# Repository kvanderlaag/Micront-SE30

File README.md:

# Micron't SE30 Beigescale Adapter
 
Micron XCEED CRT yoke board for internal greyscale on the Macintosh SE/30

If you've miraculously stumbled across one (or two) of the assorted Micron SE/30 PDS video cards which have the connector for internal greyscale output, the piece you may be missing is the board which slaps onto the back of the CRT to let it run greyscale rather than black and white. (Also the associated adapter harness.)
 
As far as I know, these have been cloned many times, and sold by various parties. All of these clones are largely derived from [Gamba's original work to this end](http://web.archive.org/web/20010626004329/http://www.accesscom.com/~gamba/microngray.html), which is no longer actively available, but by the mercy of the [internet gods](https://www.archive.org) still archived. This board doesn't provide anything that the others don't -- it's also just a straight clone, though the routing and component placement is a little more closely derived from [D.S. Larsen's photos of the original Micron board.](http://web.archive.org/web/20010626004329/http://www.eskimo.com/~dslarsen/micron/)
 
The two important things about this design are:
1. That it was created on 14-10-2022, using footprints for parts that are actively available at this time, and
2. _That it actually fuckin' exists on GitHub, with an open license._ 
 
Take it, build it, fix it, improve it, use it to make a death ray; I don't care, just _actually do something with it_, because finding someone who will actually sell you one of these today is _annoyingly difficult_.
 
## Known Issues

There is currently one _massive_ caveat: I haven't actually built one of these yet. Everything appears to be lined up to the original board fairly accurately, and I'm confident in the routing relative to the original board and the schematic, but the one thing that concerns me is the footprint for the tube socket. The footprint was created with [this 7-pin miniature (B7G) tube socket, P/N B7G-PCB](http://www.pacifictv.ca/socket.htm) in mind, since the dimensions are provided, but I've also ordered a couple of tube sockets from Aliexpress; if those don't quite fit, I'll create a second version of the board with an updated footprint, just so that there's options for tube socket sourcing, since that seems like it could be a pain in the ass.

Also, obviously, since I haven't built it yet, there's no guarantee it won't blow up your SE/30, or your video card. Since both of these are quite expensive, maybe double check it against Gamba's (known-working) source material before you go build it. I'm not infallible -- in fact, I'm not even that smart -- but I'm also not your dad, so do what you want.

I still need to create a KiCAD schematic of the adapter harness, too.

## Bill of Materials

If you want to actually build this, you probably need some parts to do so. These are the parts the board was designed for; other parts with similar size, lead spacing, and characteristics will probably work fine.

| Quantity | Reference | Part Number             | Description                                      | Link                                                       | Alternate                                       |
| -------- | --------- | -------------           | -------------------------------------------      | ---------------------------------------------------------- | ----------------------------------------------- |
| 3        | C1,2,3    | CK45-E3AD103ZYVNA       | Capacitor, ceramic disc, 0.01uF 1KVDC            | https://www.mouser.ca/ProductDetail/810-CK45-E3AD103ZYVN   |                                                 |
| 1        | C4        | ESS106M050AE2AA         | Capacitor, electrolytic, 10uF, 50VDC, 105°C      | https://www.mouser.ca/ProductDetail/80-ESS106M050AE2AA     |                                                 |
| 1        | C5        | UVZ1A470MDD             | Capacitor, electrolytic, 47uF, 10VDC, 105°C      | https://www.mouser.ca/ProductDetail/647-UVZ1A470MDD        |                                                 |
| 1        | C6        | R82EC3100DQ70J          | Capacitor, film, 0.1uF, 100VDC                   | https://www.mouser.ca/ProductDetail/80-R82EC3100DQ70J      |                                                 |
| 1        | C7        | K104Z15Y5VE5TL2         | Capacitor, multi-layered ceramic, 0.1uF, 25VDC   | https://www.mouser.ca/ProductDetail/594-K104Z15Y5VE5TL2    |                                                 |
| 1        | C8        | UVZ1C101MDD             | Capacitor, electrolytic, 100uF, 16VDC, 105°C     | https://www.mouser.ca/ProductDetail/647-UVZ1C101MDD        |                                                 |
| 1        | C9        | UPW1J101MPD6            | Capacitor, electrolytic, 100uF, 63VDC, 105°C     | https://www.mouser.ca/ProductDetail/647-UPW1J101MPD6       |                                                 |
| 3        | D1,2,3    | 1N914BTR                | Diode, 1N914A                                    | https://www.mouser.ca/ProductDetail/512-1N914BTR           |                                                 |
| 1        | J1        | 39-29-1088              | Connector, 8 pin, right-angle; Molex 5569 series | https://www.mouser.ca/ProductDetail/538-39-29-1088         |                                                 |
| 2        | L1,2      | 78F270J-RC              | Inductor, 27 uH 5%                               | https://www.mouser.ca/ProductDetail/542-78F270-RC          |                                                 |
| 2        | Q1,2      | 2N5550TFR               | Transistor, NPN                                  | https://www.mouser.ca/ProductDetail/512-2N5550TFR          |                                                 |
| 1        | Q3        | PN2222ABU               | Transistor, NPN                                  | https://www.mouser.ca/ProductDetail/512-PN2222ABU          |                                                 |
| 2        | R1,2      | CFR200JT-73-1K          | Resistor, 1.0K ohms,   2W   5%                   | https://www.mouser.ca/ProductDetail/YAGEO/CFR200JT-73-1K   |                                                 |
| 1        | R3        | CFR-25JB-52-75R         | Resistor,   75 ohms, 1/4W   5%                   | https://www.mouser.ca/ProductDetail/YAGEO/CFR-25JB-52-75R  |                                                 |
| 1        | R4        | CFR-25JR-52-300R        | Resistor,  300 ohms, 1/4W   5%                   | https://www.mouser.ca/ProductDetail/YAGEO/CFR-25JR-52-300R |                                                 |
| 1        | R5        | CFR-25JT-52-56R         | Resistor,   56 ohms, 1/4W   5%                   | https://www.mouser.ca/ProductDetail/YAGEO/CFR-25JT-52-56R  |                                                 |
| 1        | R6        | CFR-25JT-52-200R        | Resistor,  200 ohms, 1/4W   5%                   | https://www.mouser.ca/ProductDetail/YAGEO/CFR-25JT-52-200R |                                                 |
| 1        | R7        | CFR-25JT-52-12K         | Resistor,  12K ohms, 1/4W   5%                   | https://www.mouser.ca/ProductDetail/YAGEO/CFR-25JT-52-12K  |                                                 |
| 1        | R8        | CFR-25JB-52-1K5         | Resistor, 1.5K ohms, 1/4W   5%                   | https://www.mouser.ca/ProductDetail/YAGEO/CFR-25JB-52-1K5  |                                                 |
| 3        | R9,10,11  | CFR50SJT-52-100K        | Resistor, 100K ohms, 1/2W   5%                   | https://www.mouser.ca/ProductDetail/YAGEO/CFR50SJT-52-100K |                                                 |
| 1        | RV1       | PT10LH01-201A2020-S     | Resistor, variable, 200 ohms                     | https://www.mouser.ca/ProductDetail/531-PT10H-200-S        |                                                 |
| 1        | V1        | APCO EIA-1210 / B7G-PCB | Socket, CRT, 7 pin miniature, PC mount           | http://www.pacifictv.ca/socket.htm                         | https://www.aliexpress.com/item/1549957333.html |

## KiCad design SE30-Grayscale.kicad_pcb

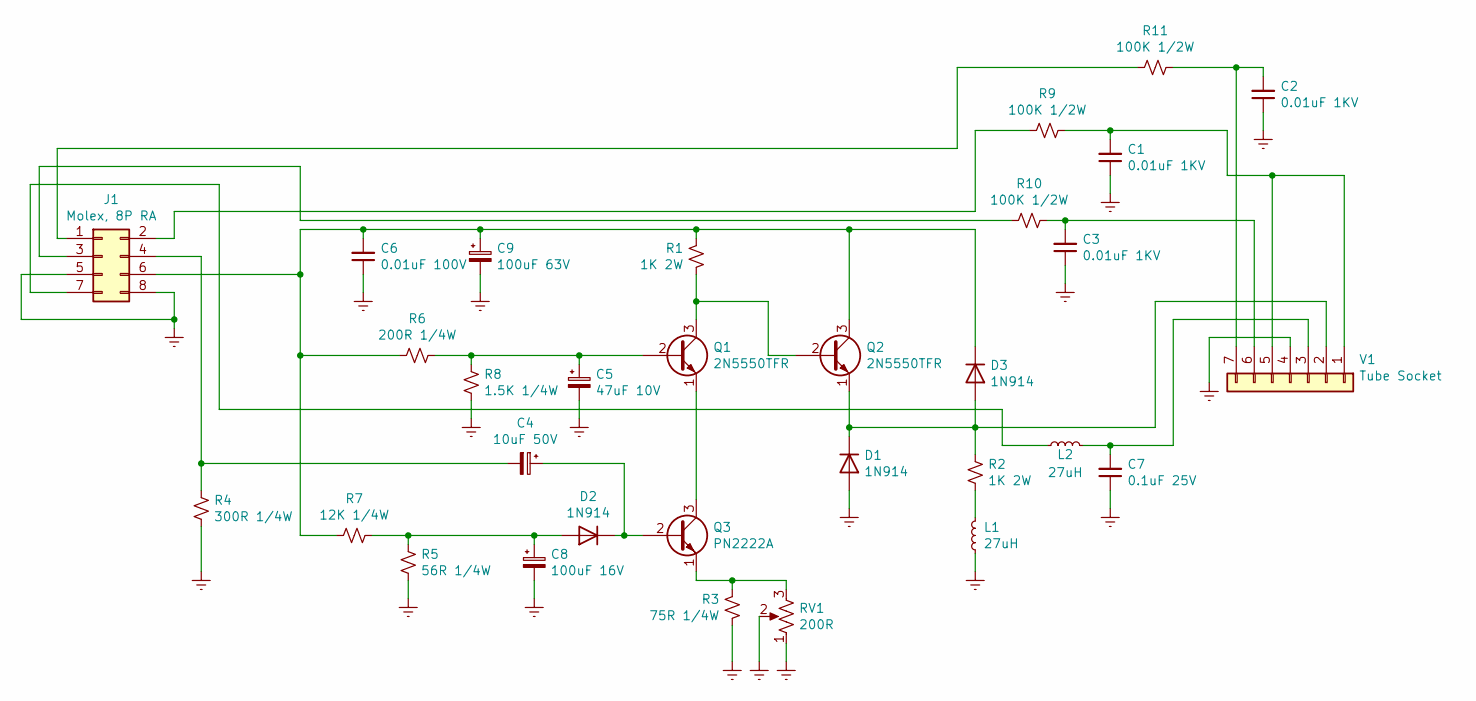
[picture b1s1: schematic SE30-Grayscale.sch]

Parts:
C1, C2, C3: 0.01uF 1KV; C_Disc_D11.0mm_W5.0mm_P7.50mm
C4: 10uF 50V; CP_Radial_D6.3mm_P2.50mm
C5: 47uF 10V; CP_Radial_D5.0mm_P2.00mm
C6: 0.01uF 100V; C_Rect_L7.2mm_W2.5mm_P5.00mm_FKS2_FKP2_MKS2_MKP2
C7: 0.1uF 25V; C_Rect_L4.6mm_W2.0mm_P2.50mm_MKS02_FKP02
C8: 100uF 16V; CP_Radial_D5.0mm_P2.00mm
C9: 100uF 63V; CP_Radial_D8.0mm_P3.50mm
D1, D2, D3: 1N914; D_DO-35_SOD27_P7.62mm_Horizontal
J1: Molex, 8P RA; Molex
L1, L2: 27uH; L_Axial_L7.0mm_D3.3mm_P12.70mm_Horizontal_Fastron_MICC
Q1, Q2: 2N5550TFR; TO-92_Inline_Wide
Q3: PN2222A; TO-92_Inline_Wide
R1, R2: 1K 2W; R_Axial_DIN0617_L17.0mm_D6.0mm_P20.32mm_Horizontal
R3: 75R 1/4W; R_Axial_DIN0207_L6.3mm_D2.5mm_P7.62mm_Horizontal
R4: 300R 1/4W; R_Axial_DIN0207_L6.3mm_D2.5mm_P7.62mm_Horizontal
R5: 56R 1/4W; R_Axial_DIN0207_L6.3mm_D2.5mm_P7.62mm_Horizontal
R6: 200R 1/4W; R_Axial_DIN0207_L6.3mm_D2.5mm_P7.62mm_Horizontal
R7: 12K 1/4W; R_Axial_DIN0207_L6.3mm_D2.5mm_P7.62mm_Horizontal
R8: 1.5K 1/4W; R_Axial_DIN0207_L6.3mm_D2.5mm_P7.62mm_Horizontal
R9, R10, R11: 100K 1/2W; R_Axial_DIN0411_L9.9mm_D3.6mm_P12.70mm_Horizontal
RV1: 200R; Trimmer_Res_Amphenol
V1: Tube Socket; Tube-7pin-Mini

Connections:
Earth: C1.1, C2.1, C3.1, C5.2, C6.1, C7.1, C8.2, C9.2, D1.2 (A), J1.5, J1.8, L1.1, R3.1, R4.1, R5.2, R8.1, RV1.1, RV1.2, V1.4
unnamed: C1.2, R9.1, V1.1, V1.5
unnamed: C2.2, R11.1, V1.7
unnamed: C3.2, R10.1, V1.6
unnamed: C4.1, D2.1 (K), Q3.2 (B)
unnamed: C4.2, J1.4, R4.2
unnamed: C5.1, Q1.2 (B), R6.1, R8.2
unnamed: C6.2, C9.1, D3.1 (K), J1.6, Q2.3 (C), R1.2, R6.2, R7.1
unnamed: C7.2, L2.2, V1.3
unnamed: C8.1, D2.2 (A), R5.1, R7.2
unnamed: D1.1 (K), D3.2 (A), Q2.1 (E), R2.2, V1.2
unnamed: J1.1, R11.2
unnamed: J1.2, R9.2
unnamed: J1.3, R10.2
unnamed: J1.7, L2.1
unnamed: L1.2, R2.1
unnamed: Q1.1 (E), Q3.3 (C)
unnamed: Q1.3 (C), Q2.2 (B), R1.1
unnamed: Q3.1 (E), R3.2, RV1.3

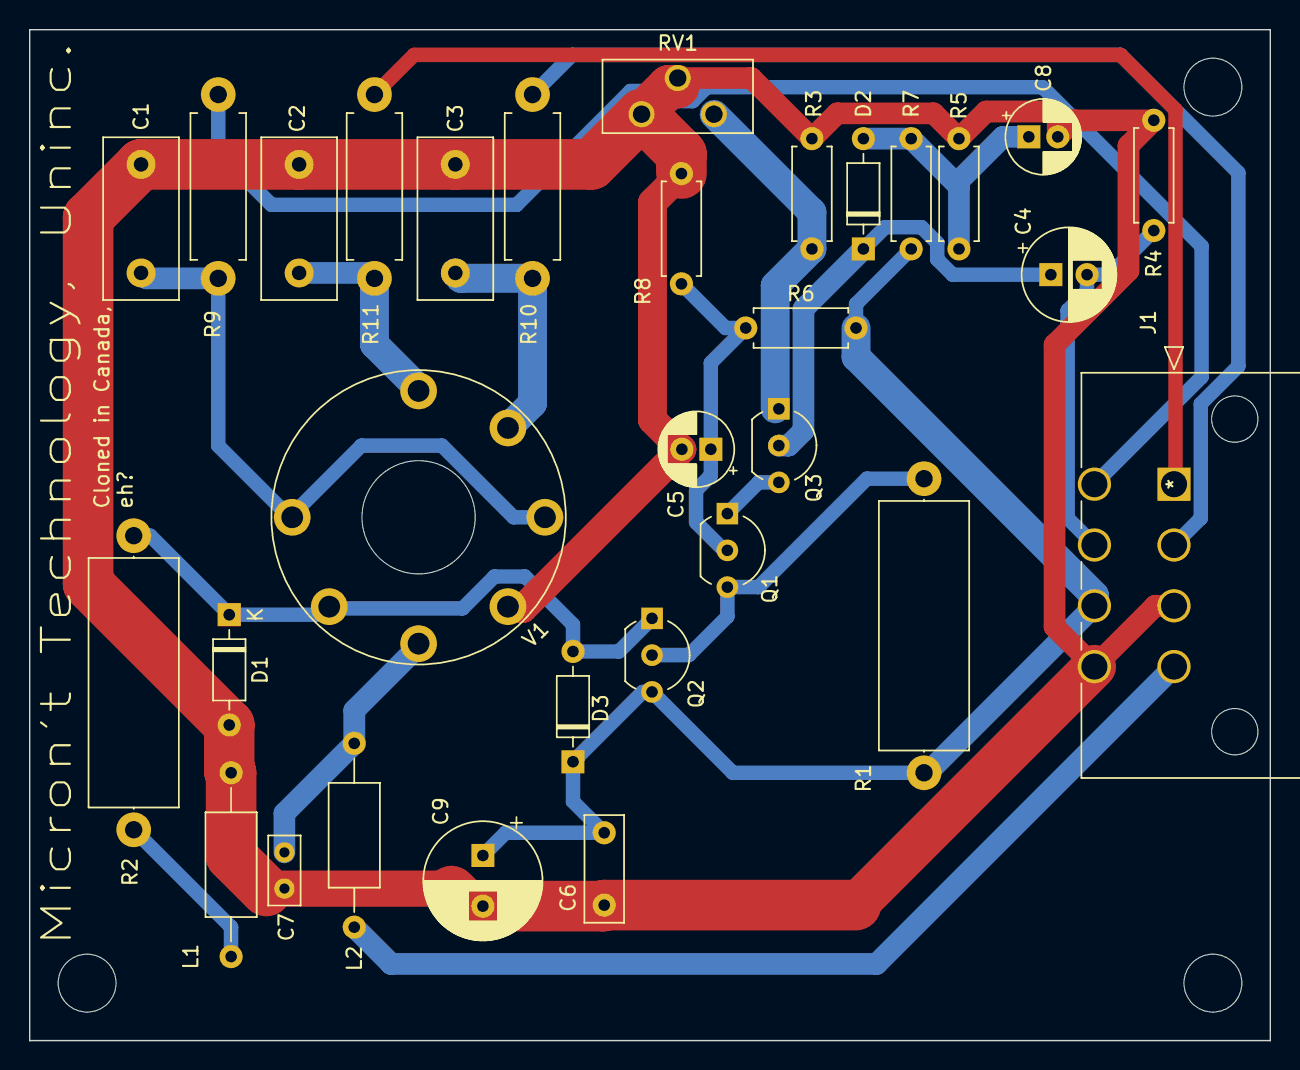
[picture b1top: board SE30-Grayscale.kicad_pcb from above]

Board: 2 copper layers, 85.7 x 69.8 mm, 31 parts (0 on the bottom side), 19 nets.

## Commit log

2022-10-14 Add images
2022-10-17 Updated tube socket footprint
    This matches the specification listed on the Pacific TV website for the 7-pin miniature tube socket they sell; the old footprint probably would have fit fine, since it was close, but why risk it?

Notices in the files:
parts and their libraries:
Copyright 2021 Accelerated Designs. All rights reserved.
